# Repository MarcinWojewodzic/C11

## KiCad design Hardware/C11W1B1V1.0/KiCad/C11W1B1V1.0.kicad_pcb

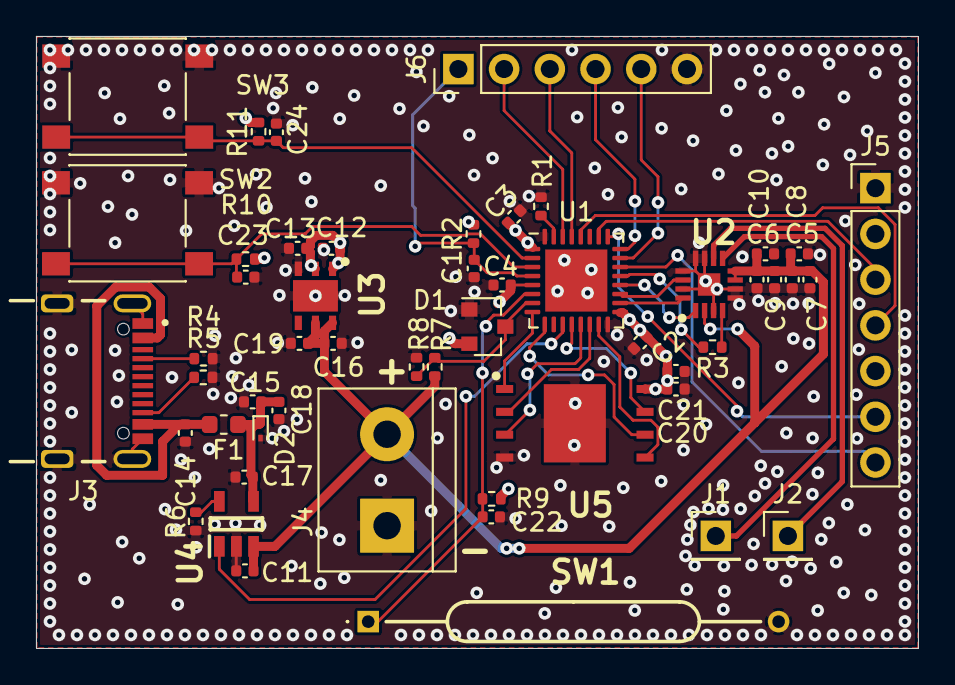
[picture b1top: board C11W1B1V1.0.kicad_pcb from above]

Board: 4 copper layers, 49.0 x 34.0 mm, 52 parts (0 on the bottom side), 36 nets.

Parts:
C1, C10, C12, C14, C15, C19, C20, C22, C23, C24: 100n/16V/X5R; C_0402_1005Metric
C2, C3, C4, C5, C6, C7, C8, C9, C11, C13, C16, C17, C18, C21: 4.7u/16V/X5R; C_0402_1005Metric
D1: BAT54S; SOT-23
D2: ESD9B5.0ST5G; D_SOD-923
F1: 0686F2000-01; Fuse_0603_1608Metric
J1: SPEAKER+; PinHeader_1x01_P2.54mm_Vertical
J2: SPEAKER-; PinHeader_1x01_P2.54mm_Vertical
J3: USB4105GFA120; GCT_USB4105GFA120
J4: Conn_01x02_Male; TerminalBlock_bornier-2_P5.08mm
J5: SSD1306; PinHeader_1x07_P2.54mm_Vertical
J6: Conn_01x06; PinHeader_1x06_P2.54mm_Vertical
R1, R2, R4, R5, R6, R10, R11: 10k/1%/0.063W; R_0402_1005Metric
R3: 0R; R_0402_1005Metric
R7, R8: 100k/1%/0.063W; R_0402_1005Metric
R9: 10Meg/1%/0.063W; R_0402_1005Metric
SW1: ORD3242030AT
SW2, SW3: SW_Push; SW_Push_1P1T_NO_6x6mm_H9.5mm
U1: STM32L431KBUx; QFN-32-1EP_5x5mm_P0.5mm_EP3.45x3.45mm
U2: QFN50P300X300X80-17N
U3: SON95P300X300X100-7N-D
U4: SOT95P280X110-5N
U5: SON127P800X600X80-9N-D

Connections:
+3V3: C2.2, C3.2, C4.2, C12.1, C13.1, C20.2, C21.2, D1.2, J5.2, R2.2, R9.2, R10.2, R11.2, U1.1, U1.5, U1.17, U3.1, U3.2, U5.8
+BATT: C5.1, C6.1, C7.1, C8.1, C9.1, C10.1, C11.1, C16.2, C19.2, J4.2, R7.2, U2.2, U2.7, U2.8, U3.5, U3.6, U4.3
/uC/FLASH_CLK: U1.9, U5.6
/uC/FLASH_CS: U1.8, U5.1
/uC/FLASH_IO0: U1.15, U5.5
/uC/FLASH_IO1: U1.14, U5.2
/uC/FLASH_IO2: U1.13, U5.3
/uC/FLASH_IO3: U1.12, U5.7
/uC/RX: J6.2, U1.30
/uC/SWCLK: J6.4, U1.24
/uC/SWDIO: J6.5, U1.23
/uC/TX: J6.3, U1.29
/uC/~NRST: C1.1, J6.1, R2.1, U1.4
BATT: D1.3, R7.1, R8.2, U1.7
BUTTON_1: C23.1, R10.1, SW2.1, U1.3
BUTTON_2: C24.1, R11.1, SW3.1, U1.2
CS: J5.7, U1.22
DC: J5.6, U1.25
GND: C1.2, C2.1, C3.1, C4.1, C5.2, C6.2, C7.2, C8.2, C9.2, C10.2, C11.2, C12.2, C13.2, C14.2, C15.2, C16.1, C17.1, C18.1, C19.1, C20.1, C21.1, C22.2, C23.2, C24.2, D1.1, D2.2, J3.A1_B12, J3.B1_A12, J3.SH1, J3.SH2, J3.SH3, J3.SH4, J4.1, J5.1, J6.6, R1.1, R4.1, R5.2, R6.2, R8.1, SW1.2, SW2.2, SW3.2, U1.16, U1.32, U1.33, U2.3, U2.5, U2.6, U2.11, U2.12, U2.13, U2.15, U2.17, U3.3, U3.7, U4.2, U5.4, U5.9
MOSI: J5.4, U1.28
unnamed: C14.1, F1.2, J3.A4_B9, J3.B4_A9
unnamed: J1.1, U2.9
unnamed: J2.1, U2.10
unnamed: J3.A5, R4.2
unnamed: J3.B5, R5.1
unnamed: R1.2, U1.31
unnamed: R3.1, U2.4
unnamed: R6.1, U4.5
RS: C22.1, R9.1, SW1.1, U1.6
SAI_FS: U1.19, U2.14
SAI_SCK: U1.18, U2.16
SAI_SD: U1.20, U2.1
SCK: J5.3, U1.26
VBUS: C15.1, C17.2, C18.2, D2.1, F1.1, U4.4
~CHRG_STATUS: U1.11, U4.1
~SD_MODE: R3.2, U1.21
